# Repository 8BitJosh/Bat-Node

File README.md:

# Bat-Node
Rechargeable Wireless, Arduino compatible IOT node

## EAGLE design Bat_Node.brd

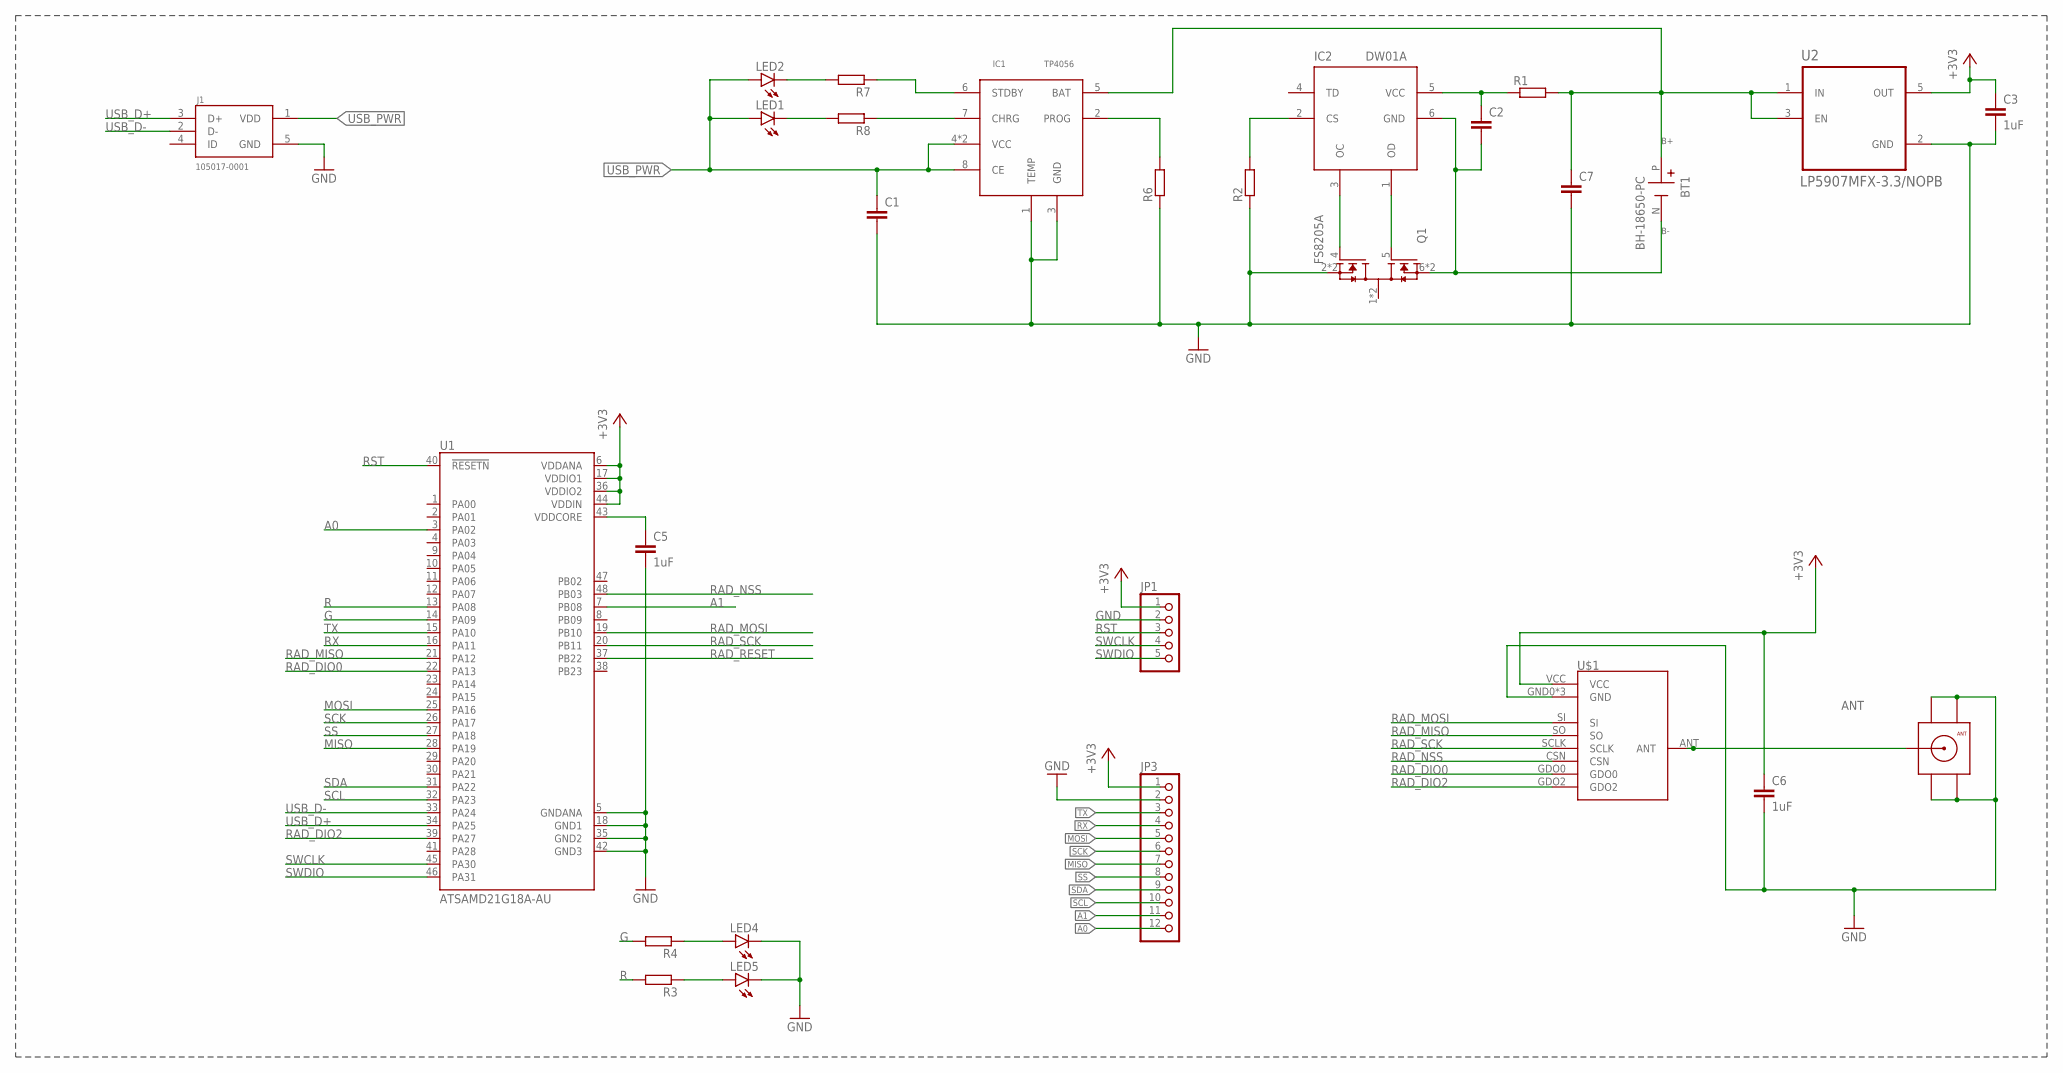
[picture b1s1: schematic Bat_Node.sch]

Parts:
BT1: BH-18650-PC; BAT_BH-18650-PC
C1, C2, C7: C-EUC0603; C0603
C3, C5, C6: 1uF; C0603
IC1: TP4056; SOP-8
IC2: DW01A; SOT23-6
J1: 105017-0001; MOLEX_105017-0001
JP1: PINHD-1X5; 1X05
JP3: PINHD-1X12; 1X12
LED1, LED2, LED4, LED5: LEDCHIP-LED0603; CHIP-LED0603
Q1: FS8205A; SOP65P640X120-8N
R1, R2, R6, R7, R8: R-EU_R0603; R0603
R3, R4: RR0603; R0603
U1: ATSAMD21G18A-AU; QFP50P900X900X120-48N
U2: LP5907MFX-3.3/NOPB; SOT95P280X145-5N
U$1: CC1101SMD; CC1101-SMD
U$6: CON-SMA-EDGE-S

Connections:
+3V3: C3.1, C6.1, JP1.1, JP3.1, U1.6 (VDDANA), U1.17 (VDDIO1), U1.36 (VDDIO2), U1.44 (VDDIN), U2.5 (OUT), U$1.VCC
A0: JP3.12, U1.3 (PA02)
A1: JP3.11, U1.7 (PB08)
ANT: U$1.ANT, U$6.P$3 (SIG)
B+: BT1.P (+), C7.1, IC1.5 (BAT), R1.2, U2.1 (IN), U2.3 (EN)
B-: BT1.N (-), C2.2, IC2.6 (GND), Q1.6 (S2), Q1.7 (S2)
G: R4.2, U1.14 (PA09)
GND: C1.2, C3.2, C5.2, C6.2, C7.2, IC1.1 (TEMP), IC1.3 (GND), J1.5 (GND), JP1.2, JP3.2, LED4.C, LED5.C, Q1.2 (S1), Q1.3 (S1), R2.1, R6.1, U1.5 (GNDANA), U1.18 (GND1), U1.35 (GND2), U1.42 (GND3), U2.2 (GND), U$1.GND0 (GND), U$1.GND1 (GND), U$1.GND2 (GND), U$6.P$1 (GND), U$6.P$2 (GND2), U$6.P$4 (GND4), U$6.P$5 (GND3)
MISO: JP3.7, U1.28 (PA19)
MOSI: JP3.5, U1.25 (PA16)
unnamed: IC2.2 (CS), R2.2
unnamed: IC2.3 (OC), Q1.4 (G1)
unnamed: IC2.1 (OD), Q1.5 (G2)
unnamed: C2.1, IC2.5 (VCC), R1.1
unnamed: C5.1, U1.43 (VDDCORE)
unnamed: IC1.2 (PROG), R6.2
unnamed: LED5.A, R3.1
unnamed: LED4.A, R4.1
unnamed: IC1.7 (CHRG), R8.1
unnamed: IC1.6 (STDBY), R7.1
unnamed: LED2.C, R7.2
unnamed: LED1.C, R8.2
R: R3.2, U1.13 (PA08)
RAD_DIO0: U1.22 (PA13), U$1.GDO0
RAD_DIO2: U1.39 (PA27), U$1.GDO2
RAD_MISO: U1.21 (PA12), U$1.SO
RAD_MOSI: U1.19 (PB10), U$1.SI
RAD_NSS: U1.48 (PB03), U$1.CSN
RAD_RESET: U1.37 (PB22)
RAD_SCK: U1.20 (PB11), U$1.SCLK
RST: JP1.3, U1.40 (!RESETN)
RX: JP3.4, U1.16 (PA11)
SCK: JP3.6, U1.26 (PA17)
SCL: JP3.10, U1.32 (PA23)
SDA: JP3.9, U1.31 (PA22)
SS: JP3.8, U1.27 (PA18)
SWCLK: JP1.4, U1.45 (PA30)
SWDIO: JP1.5, U1.46 (PA31)
TX: JP3.3, U1.15 (PA10)
USB_D+: J1.3 (D+), U1.34 (PA25)
USB_D-: J1.2 (D-), U1.33 (PA24)
USB_PWR: C1.1, IC1.4 (VCC), IC1.8 (CE), IC1.PAD (VCC), J1.1 (VDD), LED1.A, LED2.A

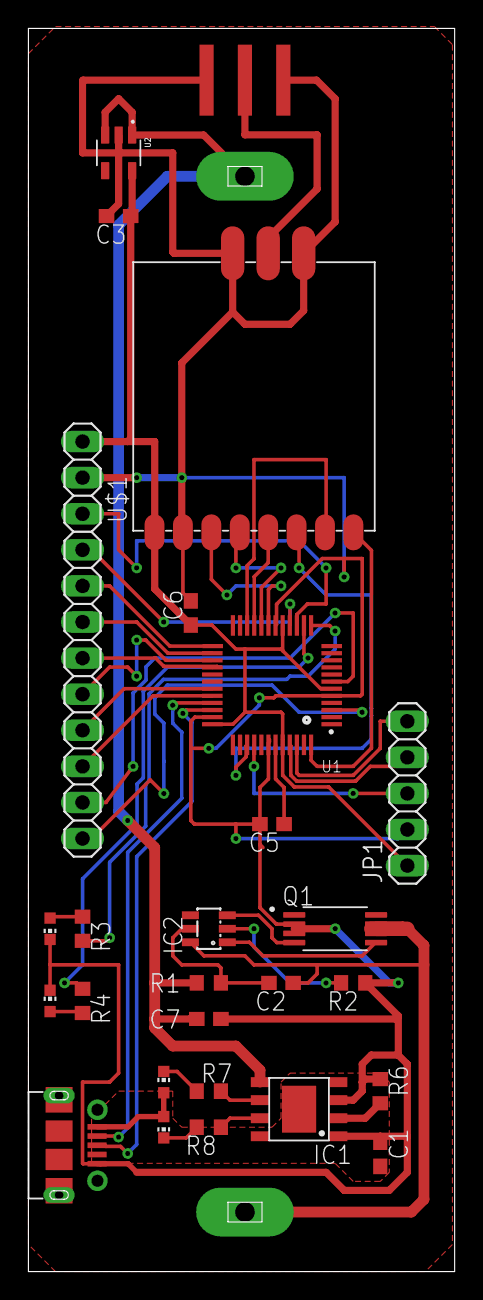
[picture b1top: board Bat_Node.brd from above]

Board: 2 copper layers, 30.0 x 87.5 mm, 28 parts (1 on the bottom side), 41 nets.

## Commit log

2020-04-08 Added board

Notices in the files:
parts and their libraries:
modules: Released under the Creative Commons Attribution 4.0 International License: http://creativecommons.org/licenses/by/4.0
